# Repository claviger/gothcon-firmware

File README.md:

# Gothcon 2026 Badge

MicroPython firmware for an ESP32-C3 convention badge with:
- Four interrupt-driven directional pushbuttons (Up/Down/Left/Right, S4–S7)
- 44 WS2812B (NeoPixel) addressable RGB LEDs on IO10 — including two "bat eye"
  LEDs (indices **28** and **30**) driven independently of the animated body
- A library of colour-agnostic **patterns** combined with selectable **palettes**
- A wireless **contagion** effect (ESP-NOW): tap Down and nearby badges adopt
  your pattern + palette, cascading a few hops through the room

**See it in action:**
[video 1](https://imgur.com/qmLkWM7) ·
[video 2](https://imgur.com/OPmR4Vh) —
or the full [photo album](https://imgur.com/a/gothcon-2026-badges-79vPE7C).

---

## Hardware

| GPIO | Function |
|------|----------|
| IO4  | Up button (S6, active-low, internal pull-up) |
| IO3  | Down button (S7, active-low, internal pull-up) |
| IO0  | Left button (S4, active-low, internal pull-up) |
| IO2  | Right button (S5, active-low, internal pull-up) |
| IO10 | WS2812B data line (44 LEDs daisy-chained; eyes at indices 28 & 30) |

The badge's **BOOT (S3)** and **RESET (S2)** buttons are separate hardware
controls (used for flashing) and are not on these GPIOs.

---

## Operating the badge

Power the badge on and it starts animating immediately. It shows one
**pattern** rendered with one **palette** — two independent axes, so any
pattern can be combined with any palette at runtime.

| Button | Location / GPIO | Action |
|--------|-----------------|--------|
| Up (S6) | IO4 | Next pattern |
| Down (S7) | IO3 | Tap: infect nearby badges with your pattern. Hold 5 s: disable wireless (see below) |
| Left (S4) | IO0 | Previous palette |
| Right (S5) | IO2 | Next palette |
| RESET (S2) | left of the microcontroller | Reboot the badge — restarts the app and re-enables contagion after an opt-out |
| BOOT (S3) | below the microcontroller, left side | Flashing only: hold while pressing RESET to force download mode (usually unnecessary — `flash.py` does this itself) |

### How the contagion works

Tapping **Down** broadcasts your current pattern + palette over ESP-NOW;
badges that hear it switch to match and re-broadcast, cascading up to ~3 hops
(~1 s per hop, so it ripples through the room rather than instantly taking it
over). Safeguards: each press has a unique id so it never loops through a
badge twice; a badge accepts at most one press per origin every 6 s and can
originate at most one press every 6 s; pressing **any** button ignores
incoming broadcasts for 10 s so nobody's selection is overwritten mid-browse.

**Don't want your pattern overwritten?** Hold **Down** for 5 seconds: all
LEDs flash white for half a second, then wireless turns fully off — the badge
keeps its look and ignores (and stops sending) all broadcasts. Press
**RESET** (or power-cycle) to re-enable the contagion.

### Updating the badge

Two layers are installed separately — full details in
[Flashing](#flashing) below:

1. **MicroPython firmware** (the runtime `.bin`): `python flash.py --firmware`
2. **The badge application** (this repo's `src/`): `python flash.py --deploy`

Or both in one pass: `python flash.py --firmware --deploy`.

You will never need to update the MicroPython firmware to use the badge as intended;
you would only need to do that for your own badge hacking projects. So usually only
the second step is needed.

### Patterns & palettes

**Patterns** (`src/patterns.py`):

| Pattern | Body | Eyes |
|---------|------|------|
| `solid` | All body LEDs hold the first palette colour (static) | Steady white |
| `chase` | Palette colours chase along the body | Steady white |
| `twinkle` | Body mostly off; random LEDs flash in palette colours and fade | Slow pulse |
| `wash` | One colour floods across the body, then the next washes over it | Steady white |
| `swap` | Body split into colour blocks that rotate which colour they show | Steady white |
| `breathe` | Whole body fades one colour up/down, advancing colour each breath | Counter-pulse |
| `psychedelic` | Whole body strobes through the palette in unison (all red, all orange, …), ~50 ms per colour | Steady white |

The **eyes** (indices 28 & 30) are never part of the animated body; each pattern
drives them via `leds.set_eyes()`. Default eye colour is white.

**Palettes** (0–10 brightness scale): `rainbow`, `rip`, `ember`, `ghost`,
`blood`, `amethyst`, `halloween`, `toxic`, `ocean`, `sunset`. Add more by
appending to `PALETTES` in `src/patterns.py`.

---

## Prerequisites

### Host machine (your PC)
Install Python 3.11 or higher. Download the code and run:
```
pip install -r requirements.txt
```

This installs:
- `esptool` — flash the MicroPython firmware binary
- `mpremote` — deploy Python source files to the device

### MicroPython firmware

Nothing to do by default: if `firmware/` contains no `.bin`, `flash.py`
automatically downloads a pinned MicroPython build
(`ESP32_GENERIC_C3-20260406-v1.28.0.bin`) into it on the first flash.

To use a different build, download a `.bin` from
https://micropython.org/download/ESP32_GENERIC_C3/ into `firmware/` (the
newest file there wins), or pass its path explicitly with `--firmware PATH`.

---

## Flashing

### 1. Get files

Download the code from this site (either using "Download ZIP" under the code dropdown on
this page, or just git cloning the repo. Make sure Python 3.11 or higher is installed,
and python and pip are on your path. CD into the repo folder and run
```
pip install -r requirements.txt
```
to get the ESP32 tools & drivers.

### 2. Flash MicroPython

This is not normally needed, but if desired for your own badge hacking projects, you
can update the base image and operating system.

Using Python (cross-platform):
```bash
python flash.py --firmware              # auto: newest firmware/*.bin, or download
python flash.py --firmware path/to.bin  # or explicit
```

Writing firmware hard-resets the board, so `flash.py` waits for MicroPython to
reboot — re-detecting the serial port, which can change on re-enumeration —
before deploying. No manual RESET press is usually needed, but if it hangs, just press
RESET.

### 3. Deploy the badge application

```bash
python flash.py --deploy
```

### Flashing many badges in a row

```bash
python flash.py --continuous
```

Batch mode for provisioning a stack of badges with minimal PC interaction:
plug a badge in and it is flashed + deployed automatically; unplug it when
told, plug in the next, repeat. Progress is counted per badge, a failed badge
is reported and skipped (unplug, check it, re-plug to retry), and **Ctrl+C**
ends the session. Firmware is resolved once up front (auto-download included),
so later badges never wait on the network. On a PC with other COM devices,
plug the first badge in *after* starting the command so it is detected as the
newly-appearing port. It is admittedly unlikely anyone but me will ever use
this command, since no one else has a pile of hundreds of badges.

### Flashing station (Raspberry Pi + PiTFT)

`station/deploy_button.py` turns a battery-powered Raspberry Pi with an
Adafruit 2.8" capacitive PiTFT into a portable, laptop-free badge flasher:
plug a badge into the Pi's USB, press a tactile button on the screen bezel,
and watch the output on the TFT console.

| Button | GPIO | Action |
|---|---|---|
| 1 | 23 | `flash.py --deploy` — update the badge app (fast, the common case) |
| 2 | 22 | `flash.py --firmware --deploy` — full reflash for unknown-state badges |
| 3 | 27 | hold 2 s: safe shutdown of the Pi |
| 4 | 18 | spare |

(GPIOs are for the **original** 2.8" PiTFT, product 1601; the later "Plus"
boards wire their buttons to 17/22/23/27 instead. Unsure which GPIO a
physical button is? Run `python station/deploy_button.py --identify`, press
each button, and adjust the constants at the top of the script to match.)

Presses during a running job are ignored; each job ends with a big
SUCCESS/FAILED banner and returns to READY. (For provisioning a large pile of
badges in one sitting, `flash.py --continuous` above is still the faster,
zero-button workflow.)

**Station setup** (Raspberry Pi OS, 32-bit on a Pi 2):

1. Enable the PiTFT — in `/boot/firmware/config.txt`:
   `dtparam=spi=on`, `dtparam=i2c1=on`, and the overlay matching your board —
   `dtoverlay=pitft28-resistive,rotate=90,speed=64000000,fps=30` for the
   original (1601) or `dtoverlay=pitft28-capacitive,...` for the capacitive
   models; then append `fbcon=map:10` to `/boot/firmware/cmdline.txt` to put
   the text console on the TFT.
2. `git clone` this repo, then create the venv **with system-site-packages**
   (the station script needs the OS-packaged `gpiozero`/`lgpio`, which a
   plain venv cannot see):

   ```bash
   sudo apt install -y python3-venv python3-gpiozero python3-lgpio
   python3 -m venv --system-site-packages .venv
   source .venv/bin/activate       # if activate is missing, python3-venv was
   pip install -r requirements.txt #   absent — rm -rf .venv and redo
   ```

   Then run `python flash.py --firmware` once while online to pre-seed
   `firmware/`.
3. Enable console auto-login (`raspi-config` → Boot → Console Autologin) and
   launch the station from `~/.bash_profile`:

   ```bash
   if [ "$(tty)" = "/dev/tty1" ]; then
     cd ~/gothcon-firmware && source .venv/bin/activate
     while true; do python station/deploy_button.py; sleep 2; done
   fi
   ```

## REPL access (terminal, to see debug output)

```bash
mpremote connect COM3
```

Press **Ctrl+C** to interrupt `main.py` and drop to the REPL.
Press **Ctrl+D** to soft-reset and restart `main.py`.

---

## Project structure

```
esp32c3-firmware/
├── README.md
├── Makefile              # Convenience targets: erase, flash, deploy, all
├── flash.py              # Cross-platform flash/deploy script
├── requirements.txt      # Host dependencies (esptool, mpremote)
├── firmware/
│   └── .gitkeep          # Place MicroPython .bin here
├── src/
│   ├── main.py           # Entry point — wires all modules together
│   ├── buttons.py        # GPIO interrupt + debounce (Up/Down/Left/Right)
│   ├── leds.py           # WS2812B NeoPixel driver (IO10, 44 LEDs + eyes)
│   ├── patterns.py       # Pattern/palette library (two independent axes)
│   └── contagion.py      # ESP-NOW pattern contagion (burst TX, duty-cycled RX)
└── tests/                # Host-side (CPython) unit tests — not deployed to device
    ├── harness.py        # Fake strip/pins/clock/radio + sys.path setup
    ├── test_buttons.py
    ├── test_contagion.py
    ├── test_flash.py
    ├── test_leds.py
    └── test_patterns.py
```

### Running the tests

The `leds`, `patterns`, `buttons`, and `contagion` modules are importable on a
host PC (the MicroPython hardware imports are deferred, and the test harness
fakes `machine`, `micropython`, `network`, `espnow`, and `utime`), so their
logic is covered by plain `unittest`:

```bash
python -B -m unittest discover -s tests
```

(`-B` keeps the source tree free of `__pycache__`. `flash.py --deploy` only ever
ships `src/*.py`, so stray bytecode never reaches the device regardless.)

---

## Module reference

### `buttons`

```python
import buttons

def my_callback(pin_num):
    print(f"GPIO {pin_num} pressed")

# Register all four directional buttons at once (Up, Down, Left, Right)
buttons.register_all(cb_up, cb_down, cb_left, cb_right)

# Or register individually using the named pins
buttons.register(buttons.PIN_LEFT, my_callback)
buttons.unregister(buttons.PIN_LEFT)
```

### `leds`

```python
import leds

leds.init()                      # Must call first
leds.set_all(0, 10, 0)           # Fill green, all 44 LEDs (no update yet)
leds.write()                     # Push buffer to hardware
leds.set_all_and_show(0, 0, 10)  # Fill blue + push in one call
leds.set_one(3, 10, 0, 0)        # Set LED index 3 to red
leds.set_range(0, 10, 10, 0, 0)  # Set LEDs 0-9 to dim red
leds.clear_and_show()            # All off

# Body / eye helpers (colours on the 0–10 scale)
leds.set_body_all(0, 10, 0)      # Fill only the body (eyes 28 & 30 untouched)
leds.set_body_logical(0, 10, 0, 0)  # Set the Nth body LED, skipping the eyes
leds.set_eyes(10, 10, 10)        # Set both bat eyes to white
leds.clear_body()                # Body off; eyes untouched
```

Layout constants: `leds.NUM_LEDS` (44), `leds.EYES` (`(28, 30)`),
`leds.BODY` (the 42 non-eye indices), `leds.BODY_COUNT` (42).

### `patterns`

Two independent axes — pattern index and palette index:

```python
import patterns

patterns.pattern_count();  patterns.pattern_name(i)
patterns.palette_count();  patterns.palette_name(j)
patterns.activate(pattern_i, palette_j)      # render initial frame
patterns.tick(pattern_i, palette_j, t_ms)    # advance; no-op for static patterns
```

Changing either axis simply re-calls `activate(...)`, so the running pattern
always reflects the currently selected palette.

### `contagion`

```python
import contagion

contagion.init(pattern_count, palette_count)  # radio up on CHANNEL, reset state

# Every main-loop tick:
infected = contagion.service(t_ms)     # -> (pattern, palette) or None
contagion.broadcast(p, q, t_ms)        # tap: burst our look (False if in cooldown)
contagion.notify_user_activity(t_ms)   # any button press: mute infections 10s
contagion.opt_out()                    # radio hard off until power cycle
contagion.is_enabled()
```

Packet (13 bytes, broadcast to `ff:ff:ff:ff:ff:ff` on WiFi channel 1):
`magic 0xC7 · version · origin MAC (6) · seq (u16) · TTL · pattern · palette`.
Received packets are validated (length/magic/version/TTL/index bounds),
deduplicated by `(origin, seq)` for 60 s, and re-broadcast with TTL−1 after a
0–300 ms jitter while TTL > 1.

**Battery / stability:** the radio stays active for the whole session. The
original design duty-cycled `wlan.active()` at ~1 Hz to save power, but the
~40k driver start/stop cycles per night froze badges (wifi driver
instability), so cycling is disabled pending a gentler scheme; `gc.collect()`
runs once a second to curb heap fragmentation. Senders still repeat each
packet 16× spaced 80 ms — cheap redundancy against loss. Battery impact of
the always-on radio is being measured on hardware (requirement: ≥24 h on the
2000 mAh pack). All timing constants sit at the top of `contagion.py`.
Packets are unauthenticated — anyone with an ESP32 could forge them;
accepted for a conference toy.

---

## Makefile targets

| Target | Description |
|--------|-------------|
| `make help` | Show usage |
| `make erase PORT=...` | Erase device flash |
| `make flash PORT=...` | Erase + flash MicroPython (`FIRMWARE=...` optional, default auto) |
| `make deploy PORT=...` | Copy `src/` to device filesystem |
| `make all PORT=...` | Flash + deploy (`FIRMWARE=...` optional, default auto) |

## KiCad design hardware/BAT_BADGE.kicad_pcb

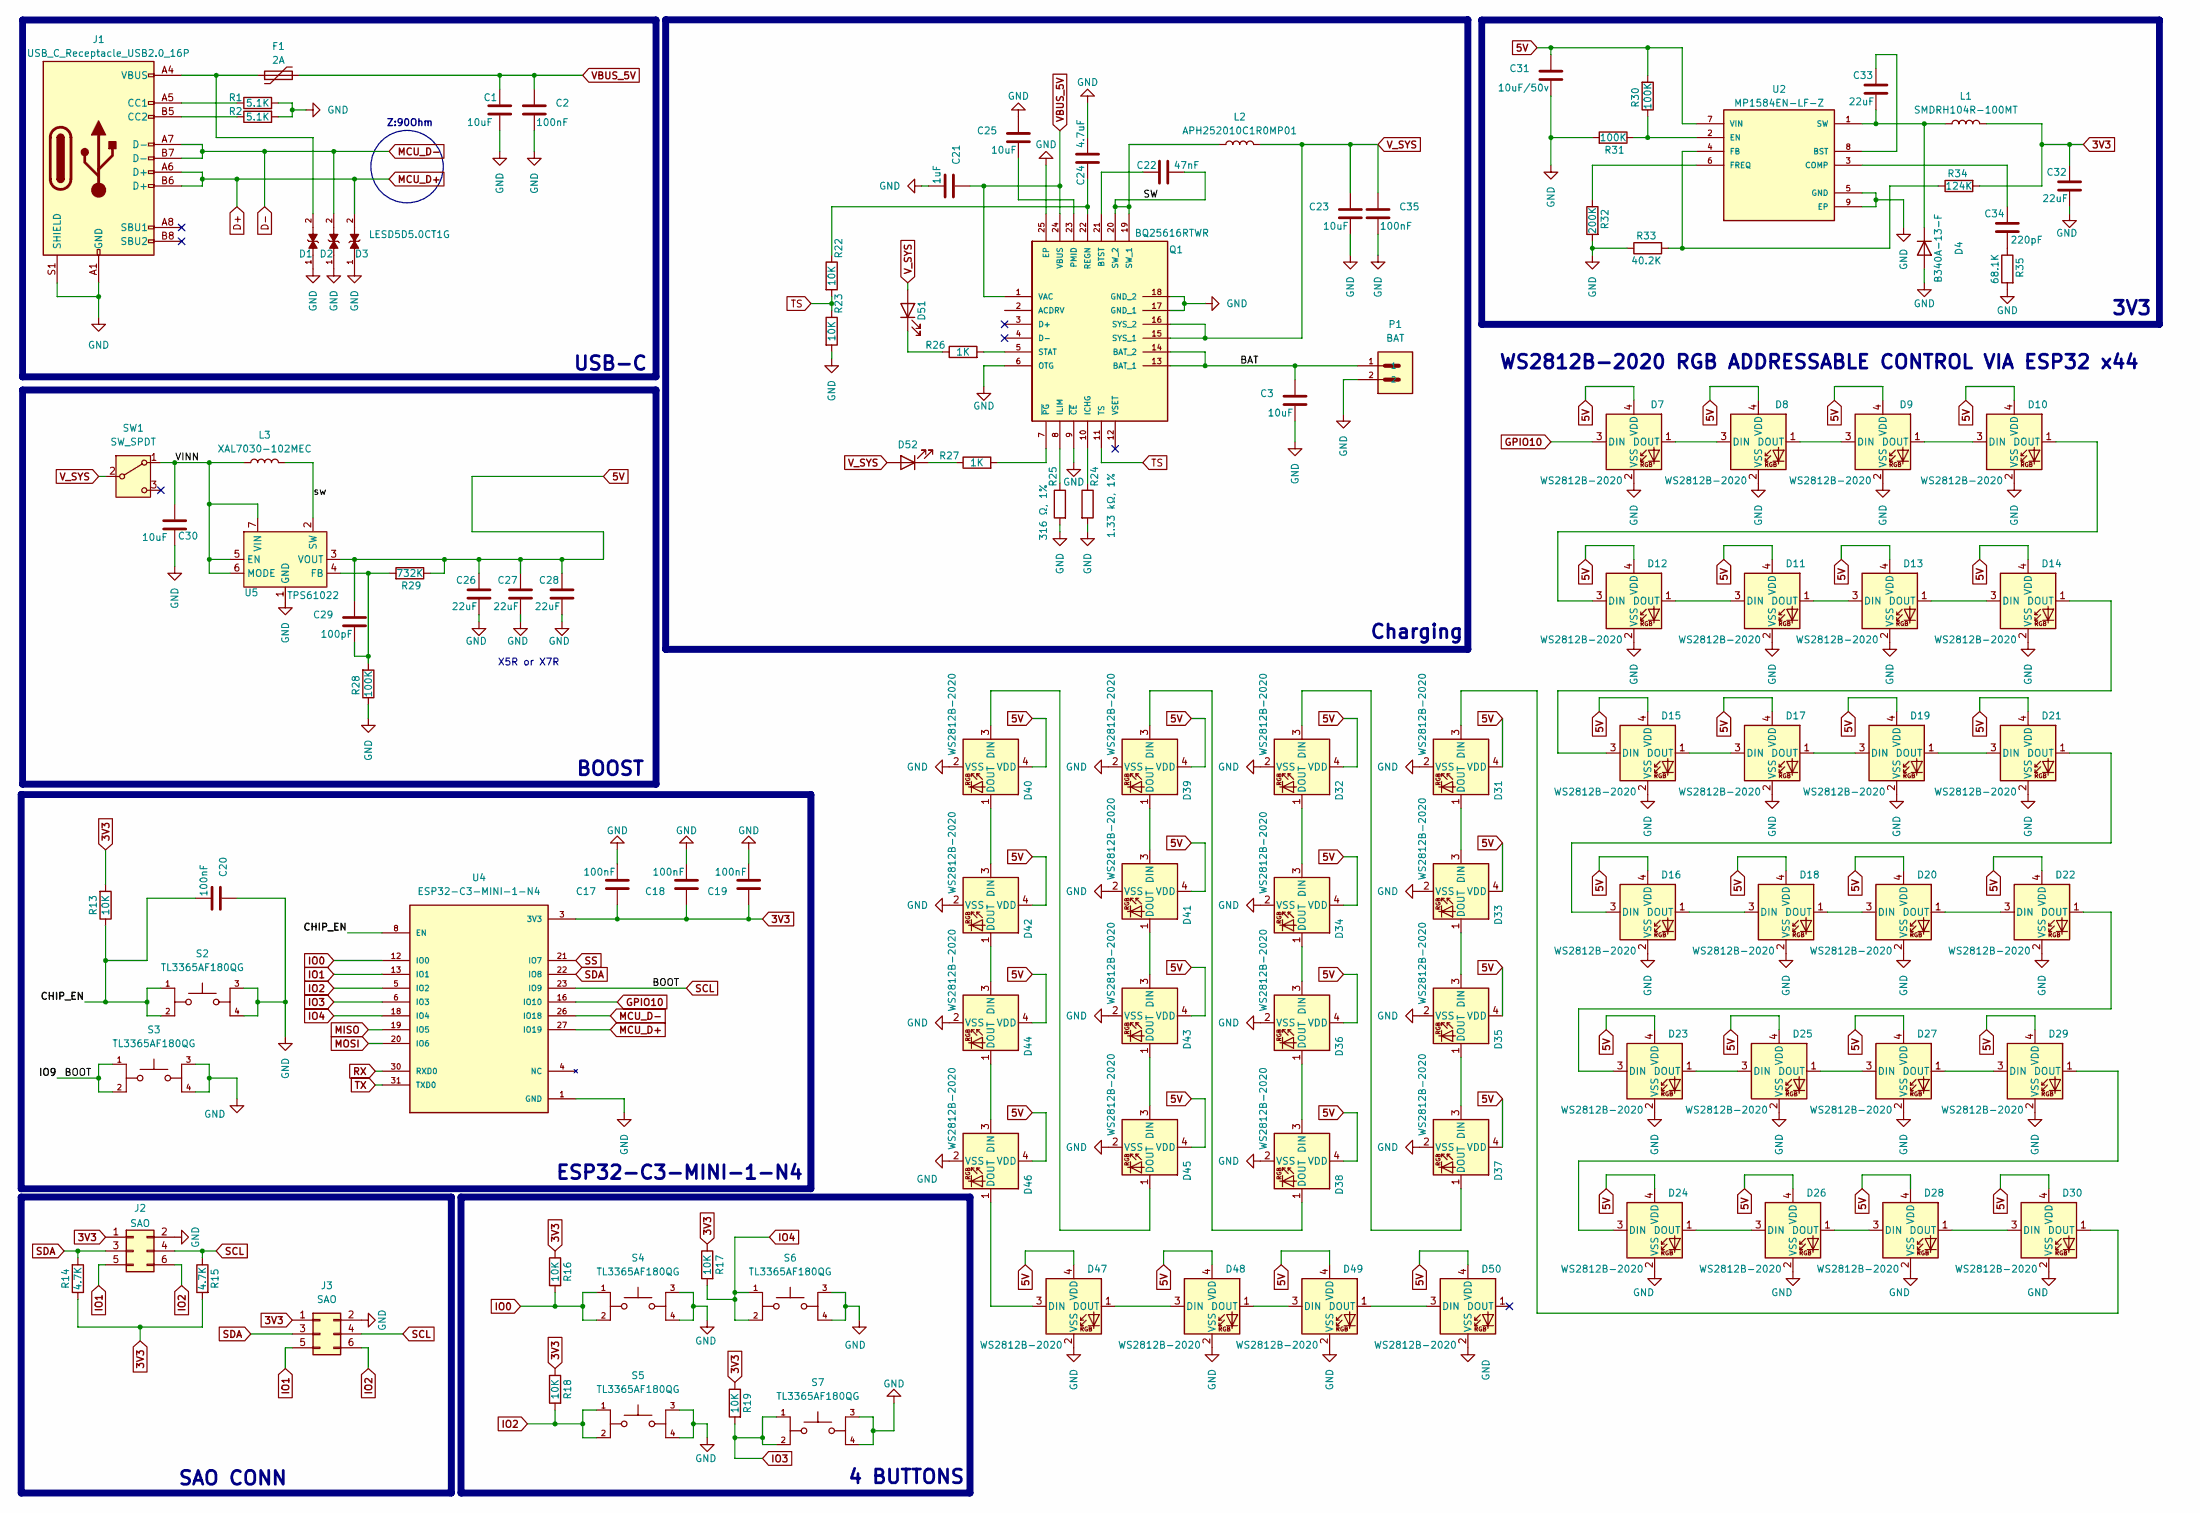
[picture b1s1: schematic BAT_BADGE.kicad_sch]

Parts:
C1, C3, C23, C25, C30: 10uF; C_0603_1608Metric
C2, C17, C18, C19, C20, C35: 100nF; C_0603_1608Metric
C21: 1uF; C_0603_1608Metric
C22: 47nF; C_0603_1608Metric
C24: 4.7uF; C_0603_1608Metric
C26, C27, C28, C32, C33: 22uF; C_0603_1608Metric
C29: 100pF; C_0603_1608Metric
C31: 10uF/50v; C_0603_1608Metric
C34: 220pF; C_0603_1608Metric
D1, D2, D3: LESD5D5.0CT1G; TVS_LESD5D5.0CT1G; PARTREV O
D4: B340A-13-F; D_SMA
D7, D8, D9, D10, D11, D12, D13, D14, D15, D16, D17, D18, D19, D20, D21, D22, D23, D24, D25, D26, D27, D28, D29, D30, D31, D32, D33, D34, D35, D36, D37, D38, D39, D40, D41, D42, D43, D44, D45, D46, D47, D48, D49, D50: WS2812B-2020; LED_WS2812B-2020_PLCC4_2.0x2.0mm
D51: CHARGING; LED_0805_2012Metric
D52: LED POWER GOOD; LED_0805_2012Metric
F1: 2A; R_1206_3216Metric
J1: USB_C_Receptacle_USB2.0_16P; USB_C_Receptacle_G-Switch_GT-USB-7010ASV
J2, J3: SAO; PinHeader_2x03_P2.54mm_Vertical
L1: SMDRH104R-100MT; L_10.4x10.4_H4.8
L2: APH252010C1R0MP01; L_1008_2520Metric
L3: XAL7030-102MEC; L_Coilcraft_XAL7030-102
P1: BAT; JST_S2B-PH-SM4-TB_LF__SN_
Q1: BQ25616RTWR; QFN50P400X400X80-25N; M_PART_NUMBER BQ25616RTWR
R1, R2: 5.1K; R_0603_1608Metric
R13, R16, R17, R18, R19, R22, R23: 10K; R_0603_1608Metric
R14, R15: 4.7K; R_0603_1608Metric
R24: 1.33 kΩ, 1%; R_0603_1608Metric
R25: 316 Ω, 1%; R_0603_1608Metric
R26, R27: 1K; R_0603_1608Metric
R28, R30, R31: 100K; R_0603_1608Metric
R29: 732K; R_0603_1608Metric
R32: 200K; R_0603_1608Metric
R33: 40.2K; R_0603_1608Metric
R34: 124K; R_0603_1608Metric
R35: 68.1K; R_0603_1608Metric
S2, S3, S4, S5, S6, S7: TL3365AF180QG; SW_TL3365AF180QG; PARTREV A
SW1: SW_SPDT
U2: MP1584EN-LF-Z; SOIC127P600X170-9N
U4: ESP32-C3-MINI-1-N4; XCVR_ESP32-C3-MINI-1-N4; PARTREV v1.0; DigiKey_Part_Number 5407-ESP32-C3-MINI-1-N4CT-ND
U5: TPS61022; Texas_RWU0007A_VQFN-7_2x2mm_P0.5mm

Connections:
3V3: C17.1, C18.1, C19.1, C32.1, J2.1, J3.1, L1.2, R13.2, R14.1, R15.2, R16.1, R17.1, R18.1, R19.1, R34.2, U4.3 (3V3)
5V: C26.1, C27.1, C28.1, C29.1, C31.1, D7.4 (VDD), D8.4 (VDD), D9.4 (VDD), D10.4 (VDD), D11.4 (VDD), D12.4 (VDD), D13.4 (VDD), D14.4 (VDD), D15.4 (VDD), D16.4 (VDD), D17.4 (VDD), D18.4 (VDD), D19.4 (VDD), D20.4 (VDD), D21.4 (VDD), D22.4 (VDD), D23.4 (VDD), D24.4 (VDD), D25.4 (VDD), D26.4 (VDD), D27.4 (VDD), D28.4 (VDD), D29.4 (VDD), D30.4 (VDD), D31.4 (VDD), D32.4 (VDD), D33.4 (VDD), D34.4 (VDD), D35.4 (VDD), D36.4 (VDD), D37.4 (VDD), D38.4 (VDD), D39.4 (VDD), D40.4 (VDD), D41.4 (VDD), D42.4 (VDD), D43.4 (VDD), D44.4 (VDD), D45.4 (VDD), D46.4 (VDD), D47.4 (VDD), D48.4 (VDD), D49.4 (VDD), D50.4 (VDD), R29.1, R30.2, U2.7 (VIN), U5.3 (VOUT)
/BAT: C3.1, P1.1, Q1.13 (BAT_1), Q1.14 (BAT_2)
/CHIP_EN: C20.2, R13.1, S2.1, S2.2, U4.8 (EN)
/SW: C22.2, L2.1, Q1.19 (SW_1), Q1.20 (SW_2)
/VINN: C30.1, L3.1, SW1.1, U5.5 (EN), U5.6 (MODE), U5.7 (VIN)
/sw: L3.2, U5.2 (SW)
D+: D3.2, J1.A6 (D+), J1.B6 (D+), U4.27 (IO19)
D-: D2.2, J1.A7 (D-), J1.B7 (D-), U4.26 (IO18)
GND: C1.2, C2.2, C3.2, C17.2, C18.2, C19.2, C20.1, C21.2, C23.2, C24.2, C25.1, C26.2, C27.2, C28.2, C30.2, C31.2, C32.2, C35.2, D1.1, D2.1, D3.1, D4.2 (A), D7.2 (VSS), D8.2 (VSS), D9.2 (VSS), D10.2 (VSS), D11.2 (VSS), D12.2 (VSS), D13.2 (VSS), D14.2 (VSS), D15.2 (VSS), D16.2 (VSS), D17.2 (VSS), D18.2 (VSS), D19.2 (VSS), D20.2 (VSS), D21.2 (VSS), D22.2 (VSS), D23.2 (VSS), D24.2 (VSS), D25.2 (VSS), D26.2 (VSS), D27.2 (VSS), D28.2 (VSS), D29.2 (VSS), D30.2 (VSS), D31.2 (VSS), D32.2 (VSS), D33.2 (VSS), D34.2 (VSS), D35.2 (VSS), D36.2 (VSS), D37.2 (VSS), D38.2 (VSS), D39.2 (VSS), D40.2 (VSS), D41.2 (VSS), D42.2 (VSS), D43.2 (VSS), D44.2 (VSS), D45.2 (VSS), D46.2 (VSS), D47.2 (VSS), D48.2 (VSS), D49.2 (VSS), D50.2 (VSS), J1.A1 (GND), J1.A12 (GND), J1.B1 (GND), J1.B12 (GND), J1.S1 (SHIELD), J2.2, J3.2, P1.2, Q1.6 (OTG), Q1.9 (~CE), Q1.17 (GND_1), Q1.18 (GND_2), Q1.25 (EP), R1.2, R2.2, R23.2, R24.2, R25.2, R28.1, R31.2, R32.2, R33.1, R35.2, S2.3, S2.4, S3.3, S3.4, S4.3, S4.4, S5.3, S5.4, S6.3, S6.4, S7.3, S7.4, U2.5 (GND), U2.9 (EP), U4.1 (GND), U4.2 (GND), U4.11 (GND), U4.14 (GND), U4.36 (GND), U4.37 (GND), U4.38 (GND), U4.39 (GND), U4.40 (GND), U4.41 (GND), U4.42 (GND), U4.43 (GND), U4.44 (GND), U4.45 (GND), U4.46 (GND), U4.47 (GND), U4.48 (GND), U4.49_1 (GND), U4.49_2 (GND), U4.49_3 (GND), U4.49_4 (GND), U4.49_5 (GND), U4.49_6 (GND), U4.49_7 (GND), U4.49_8 (GND), U4.49_9 (GND), U4.50 (GND), U4.51 (GND), U4.52 (GND), U4.53 (GND), U5.1 (GND)
GPIO10: D7.3 (DIN), U4.16 (IO10)
IO0: R16.2, S4.1, S4.2, U4.12 (IO0)
IO1: J2.5, J3.5, U4.13 (IO1)
IO2: J2.6, J3.6, R18.2, S5.1, S5.2, U4.5 (IO2)
IO3: R19.2, S7.1, S7.2, U4.6 (IO3)
IO4: R17.2, S6.1, S6.2, U4.18 (IO4)
MISO: U4.19 (IO5)
MOSI: U4.20 (IO6)
unnamed: C34.2, R35.1
unnamed: D1.2, F1.1, J1.A4 (VBUS), J1.A9 (VBUS), J1.B4 (VBUS), J1.B9 (VBUS)
unnamed: C33.2, D4.1 (K), L1.1, U2.1 (SW)
unnamed: D7.1 (DOUT), D8.3 (DIN)
unnamed: D8.1 (DOUT), D9.3 (DIN)
unnamed: D9.1 (DOUT), D10.3 (DIN)
unnamed: D10.1 (DOUT), D12.3 (DIN)
unnamed: D11.3 (DIN), D12.1 (DOUT)
unnamed: D11.1 (DOUT), D13.3 (DIN)
unnamed: D13.1 (DOUT), D14.3 (DIN)
unnamed: D14.1 (DOUT), D15.3 (DIN)
unnamed: D15.1 (DOUT), D17.3 (DIN)
unnamed: D16.3 (DIN), D21.1 (DOUT)
unnamed: D16.1 (DOUT), D18.3 (DIN)
unnamed: D17.1 (DOUT), D19.3 (DIN)
unnamed: D18.1 (DOUT), D20.3 (DIN)
unnamed: D19.1 (DOUT), D21.3 (DIN)
unnamed: D20.1 (DOUT), D22.3 (DIN)
unnamed: D22.1 (DOUT), D23.3 (DIN)
unnamed: D23.1 (DOUT), D25.3 (DIN)
unnamed: D24.3 (DIN), D29.1 (DOUT)
unnamed: D24.1 (DOUT), D26.3 (DIN)
unnamed: D25.1 (DOUT), D27.3 (DIN)
unnamed: D26.1 (DOUT), D28.3 (DIN)
unnamed: D27.1 (DOUT), D29.3 (DIN)
unnamed: D28.1 (DOUT), D30.3 (DIN)
unnamed: D30.1 (DOUT), D31.3 (DIN)
unnamed: D31.1 (DOUT), D33.3 (DIN)
unnamed: D32.3 (DIN), D37.1 (DOUT)
unnamed: D32.1 (DOUT), D34.3 (DIN)
unnamed: D33.1 (DOUT), D35.3 (DIN)
unnamed: D34.1 (DOUT), D36.3 (DIN)
unnamed: D35.1 (DOUT), D37.3 (DIN)
unnamed: D36.1 (DOUT), D38.3 (DIN)
unnamed: D38.1 (DOUT), D39.3 (DIN)
unnamed: D39.1 (DOUT), D41.3 (DIN)
unnamed: D40.3 (DIN), D45.1 (DOUT)
unnamed: D40.1 (DOUT), D42.3 (DIN)
unnamed: D41.1 (DOUT), D43.3 (DIN)
unnamed: D42.1 (DOUT), D44.3 (DIN)
unnamed: D43.1 (DOUT), D45.3 (DIN)
unnamed: D44.1 (DOUT), D46.3 (DIN)
unnamed: D46.1 (DOUT), D47.3 (DIN)
unnamed: D47.1 (DOUT), D48.3 (DIN)
unnamed: D48.1 (DOUT), D49.3 (DIN)
unnamed: D49.1 (DOUT), D50.3 (DIN)
unnamed: D51.1 (K), R26.1
unnamed: D52.1 (K), R27.1
unnamed: J1.A5 (CC1), R1.1
unnamed: J1.B5 (CC2), R2.1
unnamed: C22.1, Q1.21 (BTST)
unnamed: Q1.10 (ICHG), R24.1
unnamed: Q1.8 (ILIM), R25.1
unnamed: C25.2, Q1.23 (PMID)
unnamed: C24.1, Q1.22 (REGN), R22.1
unnamed: Q1.5 (STAT), R26.2
unnamed: Q1.7 (~PG), R27.2
unnamed: C33.1, U2.8 (BST)
unnamed: C34.1, U2.3 (COMP)
unnamed: R30.1, R31.1, U2.2 (EN)
unnamed: R33.2, R34.1, U2.4 (FB)
unnamed: R32.1, U2.6 (FREQ)
unnamed: C29.2, R28.2, R29.2, U5.4 (FB)
RX: U4.30 (RXD0)
SCL: J2.4, J3.4, R15.1, S3.1, S3.2, U4.23 (IO9)
SDA: J2.3, J3.3, R14.2, U4.22 (IO8)
SS: U4.21 (IO7)
TS: Q1.11 (TS), R22.2, R23.1
TX: U4.31 (TXD0)
VBUS_5V: C1.1, C2.1, C21.1, F1.2, Q1.1 (VAC), Q1.24 (VBUS)
V_SYS: C23.1, C35.1, D51.2 (A), D52.2 (A), L2.2, Q1.15 (SYS_1), Q1.16 (SYS_2), SW1.2

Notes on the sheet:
Z:90Ohm
3V3
USB-C
BOOST
SAO CONN
ESP32-C3-MINI-1-N4
WS2812B-2020 RGB ADDRESSABLE CONTROL VIA ESP32 x44
Charging
4 BUTTONS
X5R or X7R

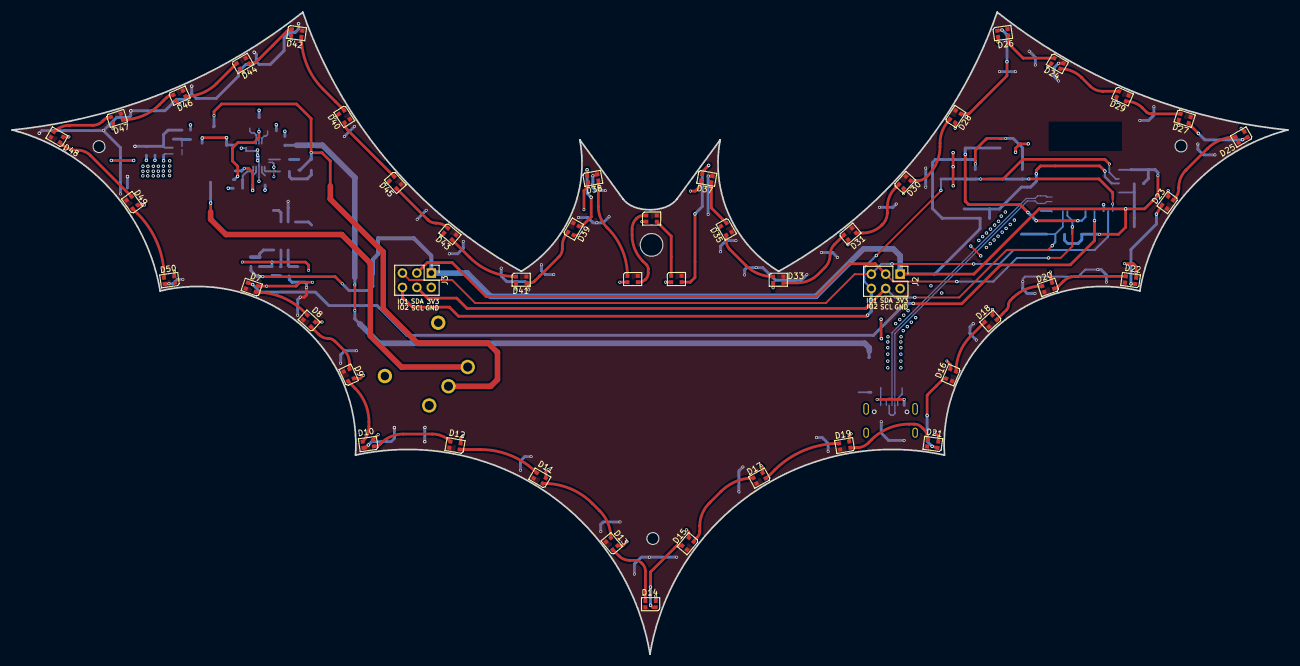
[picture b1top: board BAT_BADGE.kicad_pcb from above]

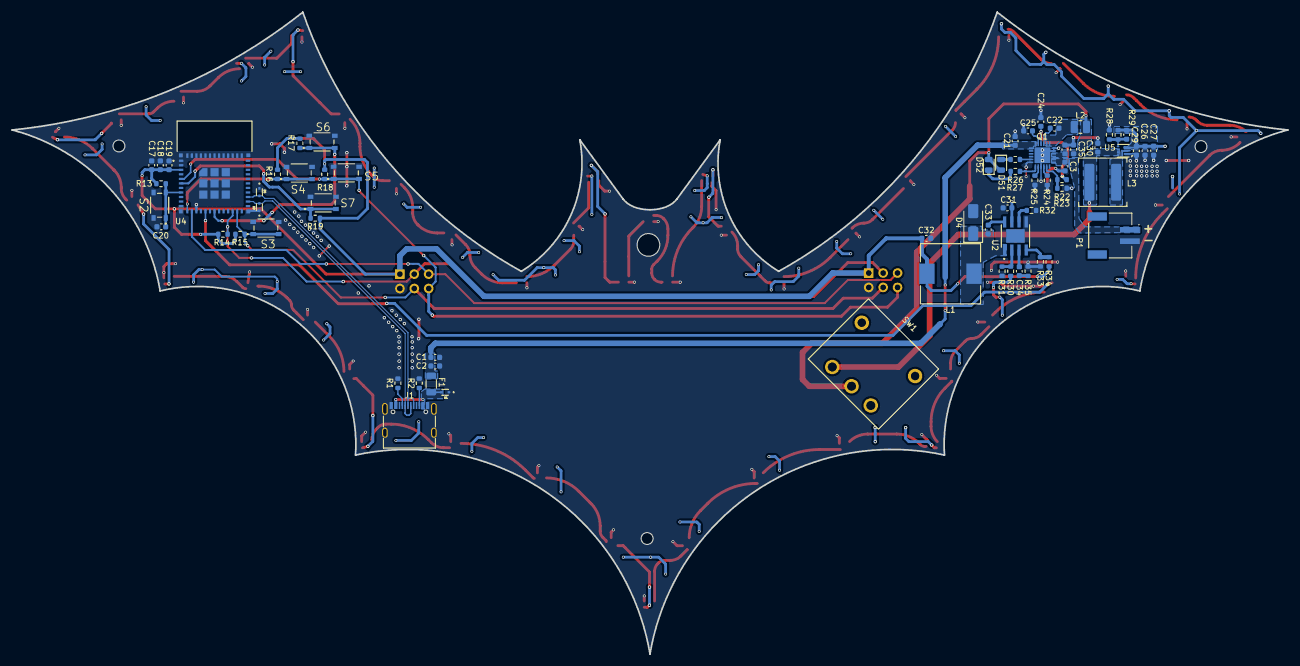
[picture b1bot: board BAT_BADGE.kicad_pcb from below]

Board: 2 copper layers, 225.0 x 113.2 mm, 114 parts (68 on the bottom side), 84 nets.

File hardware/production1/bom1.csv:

Designator,Footprint,Quantity,Value,LCSC Part #
"C1, C23, C25, C3, C30",0603,5,10uF,C70225
"C17, C18, C19, C2, C20, C35",0603,6,100nF,C45000
C21,0603,1,1uF,C1592
C22,0603,1,47nF,C115058
C24,0603,1,4.7uF,C19666
"C26, C27, C28, C32, C33",0603,5,22uF,C2762594
C29,0603,1,100pF,C519407
C31,0603,1,10uF/50v,C194427
C34,0603,1,220pF,C1603
"D1, D2, D3",TVS_LESD5D5.0CT1G,3,LESD5D5.0CT1G,"
C5246195"
"D10, D11, D12, D13, D14, D15, D16, D17, D18, D19, D20, D21, D22, D23, D24, D25, D26, D27, D28, D29, D30, D31, D32, D33, D34, D35, D36, D37, D38, D39, D40, D41, D42, D43, D44, D45, D46, D47, D48, D49, D50, D7, D8, D9",LED_WS2812B-2020_PLCC4_2.0x2.0mm,44,WS2812B-2020,C965555
D4,D_SMA,1,B340A-13-F,C18199375
D51,0805,1,CHARGING,C19273154
D52,0805,1,LED POWER GOOD,C19171391
F1,1206,1,2A,C20988
J1,USB_C_Receptacle_G-Switch_GT-USB-7010ASV,1,USB_C_Receptacle_USB2.0_16P,C2988369
SW1,"
K3-1391B-51",1,"
K3-1391B-51","
C92656"
L1,L_10.4x10.4_H4.8,1,SMDRH104R-100MT,C9935
L2,1008,1,APH252010C1R0MP01,C42455339
L3,L_Coilcraft_XAL7030-102,1,XAL7030-102MEC,C19191626
P1,JST_S2B-PH-SM4-TB_LF__SN_,1,BAT,C295747
Q1,QFN50P400X400X80-25N,1,BQ25616RTWR,C2866447
"R1, R2",0603,2,5.1K,C14677
"R13, R16, R17, R18, R19, R22, R23",0603,7,10K,C25804
"R14, R15",0603,2,4.7K,C23162
R24,0603,1,"1.33 kΩ, 1%",C22838
R25,0603,1,"316 Ω, 1%",C22987
"R26, R27",0603,2,1K,C21190
"R28, R30,R31",0603,3,100K,C14675
R29,0603,1,732K,C23239
,,,,
R32,0603,1,200K,C25811
R33,0603,1,40.2K,C137723
R34,0603,1,124K,C22788
R35,0603,1,68.1K,"
C2933251"
"S2, S3, S4, S5, S6, S7",SW_TL3365AF180QG,6,TL3365AF180QG,C2886926
U2,SOIC127P600X170-9N,1,MP1584EN-LF-Z,C15051
U4,XCVR_ESP32-C3-MINI-1-N4,1,ESP32-C3-MINI-1-N4,C2838502
U5,Texas_RWU0007A_VQFN-7_2x2mm_P0.5mm,1,TPS61022,C915088
